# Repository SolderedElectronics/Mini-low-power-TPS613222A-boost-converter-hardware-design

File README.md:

## Mini low-power TPS613222A boost converter Hardware design

|  |
| :----------------------------------------------------------: |
|      [Buy Mini low-power TPS613222A boost converter](https://www.solde.red/333096)      |

Small booster (step up) module manufactured by Soldered Electronics. It increases the input voltage to the desired level for user.

## Repository contents

All Soldered hardware is designed in KiCAD, and repositories are organized in the following way:

- CAD folder - contains KiCAD files (Schematics, Board, Panel Board), organized by version. Change log lists all changes between versions.
- OUTPUTS - contains useful files, such as Bill of Materials (BOM), PDF of schematics, 3D .step file of the board and gerber files, organized by version. 

## Want to contribute?

All contributions are welcome, feel free to submit the pull request. If you discover a bug, please submit an issue or pull request. 

## About Soldered

At Soldered, we design and manufacture a wide selection of electronic products to help you turn your ideas into acts and bring you one step closer to your final project. Our products are intented for makers and crafted in-house by our experienced team in Osijek, Croatia. We believe that sharing is a crucial element for improvement and innovation, and we work hard to stay connected with all our makers regardless of their skill or experience level. Therefore, all our products are open-source. Finally, we always have your back. If you face any problem concerning either your shopping experience or your electronics project, our team will help you deal with it, offering efficient customer service and cost-free technical support anytime. Some of those might be useful for you:

- [Web Store](https://www.soldered.com)
- [Tutorials & Projects](https://learn.soldered.com)
- [Community & Technical support](https://community.soldered.com)
- [Custom PCBs](https://pcb.soldered.com)

## License info

All Soldered open-source hardware (OSH) is under The TAPR Open Hardware License. Read more in the LICENSE file. 

No warranty - all designs in this repository are distributed in the hope that they will be useful, but without any warranty. They are provided "AS IS", therefore without warranty of any kind, either expressed or implied. The entire quality and performance of what you do with the contents of this repository are your responsibility. In no event, Soldered (TAVU) will be liable for your damages, losses, including any general, special, incidental or consequential damage arising out of the use or inability to use the contents of this repository. 

Thank you from your fellow makers at Soldered.

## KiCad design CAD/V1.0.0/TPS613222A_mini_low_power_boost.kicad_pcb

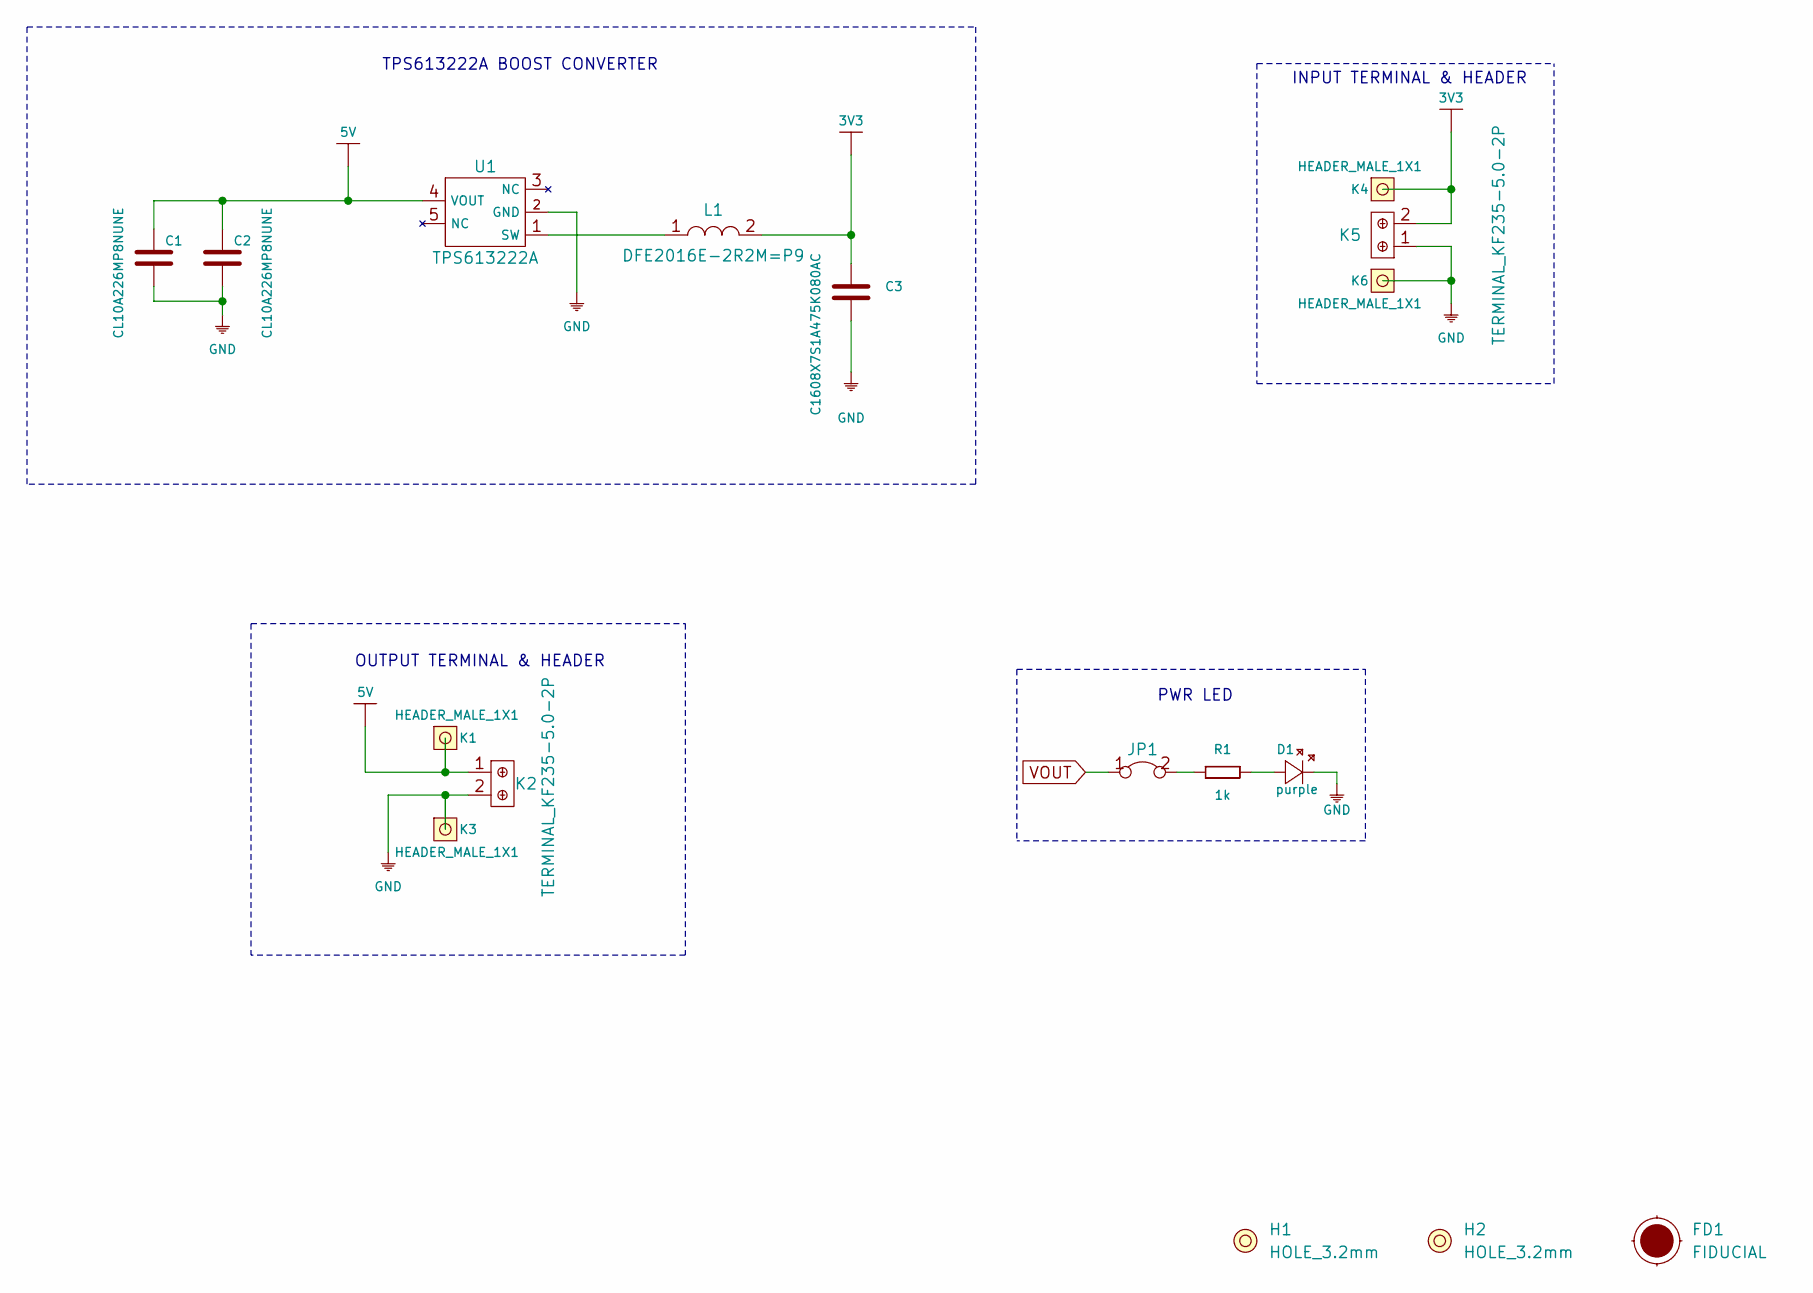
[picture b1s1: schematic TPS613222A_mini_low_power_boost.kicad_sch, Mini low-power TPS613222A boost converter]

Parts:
C1, C2: CL10A226MP8NUNE; 0805C
C3: C1608X7S1A475K080AC; 0805C
D1: purple; 0402LED
FD1: FIDUCIAL; FIDUCIAL_23
H1, H2: HOLE_3.2mm
JP1: SMD-JUMPER-CONNECTED_TRACE_SLODERMASK
K1, K3, K4, K6: HEADER_MALE_1X1
K2, K5: TERMINAL_KF235-5.0-2P
L1: DFE2016E-2R2M=P9; DFE252012F-1R0M=P2
R1: 1k; 0402R
U1: TPS613222A; tps613222a

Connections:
3V3: C3.2, K4.1, K5.2, L1.2
5V: C1.2, C2.2, K1.1, K2.1, U1.4 (VOUT)
GND: C1.1, C2.1, C3.1, D1.2 (K), K2.2, K3.1, K5.1, K6.1, U1.2 (GND)
unnamed: D1.1 (A), R1.2
unnamed: JP1.2, R1.1
unnamed: L1.1, U1.1 (SW)
VOUT: JP1.1

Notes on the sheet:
OUTPUT TERMINAL & HEADER
TPS613222A BOOST CONVERTER
PWR LED
INPUT TERMINAL & HEADER

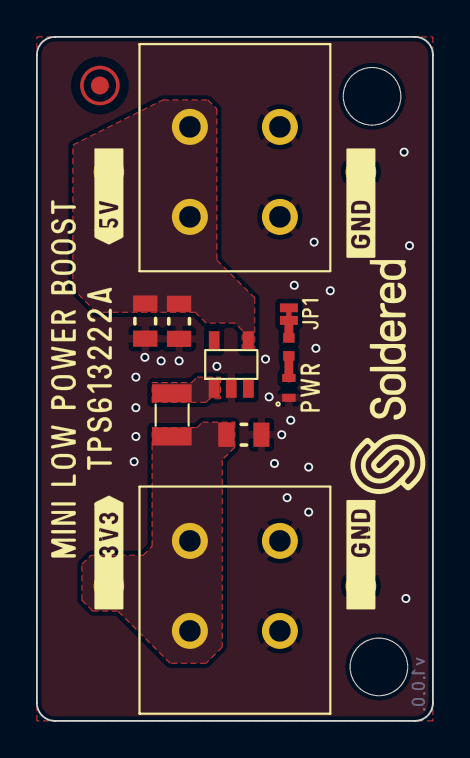
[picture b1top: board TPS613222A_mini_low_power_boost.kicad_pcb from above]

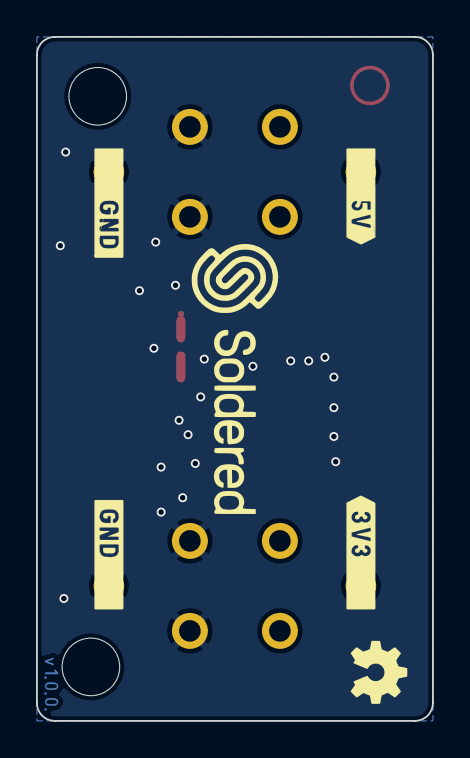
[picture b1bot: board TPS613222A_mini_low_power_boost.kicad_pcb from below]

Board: 2 copper layers, 22.0 x 38.0 mm, 18 parts (5 on the bottom side), 6 nets.

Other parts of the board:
Ref**: Val**; Version1.0.0.

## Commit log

2022-08-06 Updating open source files.
